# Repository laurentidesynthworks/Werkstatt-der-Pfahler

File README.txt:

The Werkstatt der Pfähler (Werkstatt the Impaler) is a Moog Werkstatt-Ø1 that has been cut up and extensively modified. There 
is a huge beast inside these little synths that can only be accessed through modifying.

There are 2 versions available: Standard and Full. The Standard version is perfect for incorporating into an existing Eurorack 
modular system. Most of the header patch points have been brought to the rear of the unit to 3.5mm Jacks. Most importantly, 
the EG can be triggered by an external gate. This is not possible without modification.  

The Full version takes the standard and brings it to a stand-alone powerhouse! In addition to the CV In’s and Out’s at the 
rear, buffers are added to all CV Out’s (these are circuits that keep critical voltages, like the raw VCO waveforms from 
sagging when used to drive external gear).  The CV Out’s are wired to TRS jacks, giving a total of 8 individual outputs. 
A MIDI 2 CV (MINICV) converter is added to drive the VCO and EG. Additionally, the CV & Gate generated by the MIDI 2 CV is 
brought to 2 jacks, so when the Werkstatt is not in use, it can be used to drive other analog gear that does not have MIDI,
but does have CV & Gate In’s. A mixer is added to give volume control over the Werkstatt VCO and External Audio. Additionally, 
the VCF is wired to the Audio In jack, so when nothing is plugged into the jack, the Audio In volume knob will send the VCF 
back into itself for some intense filter overdrive! A 2nd glide circuit is added in line with the VCO CV In. The Werkstatt 
Glide potentiometer is removed and replaced with a dual gang potentiometer. This way one knob can control both the Werkstatt 
glide and the external pitch glide. The VCO Wave selector switch is removed and a mixer circuit is added so the 2 waveforms 
can be continuously blended from one to the other. Lastly, there is a Fine Tune knob added.

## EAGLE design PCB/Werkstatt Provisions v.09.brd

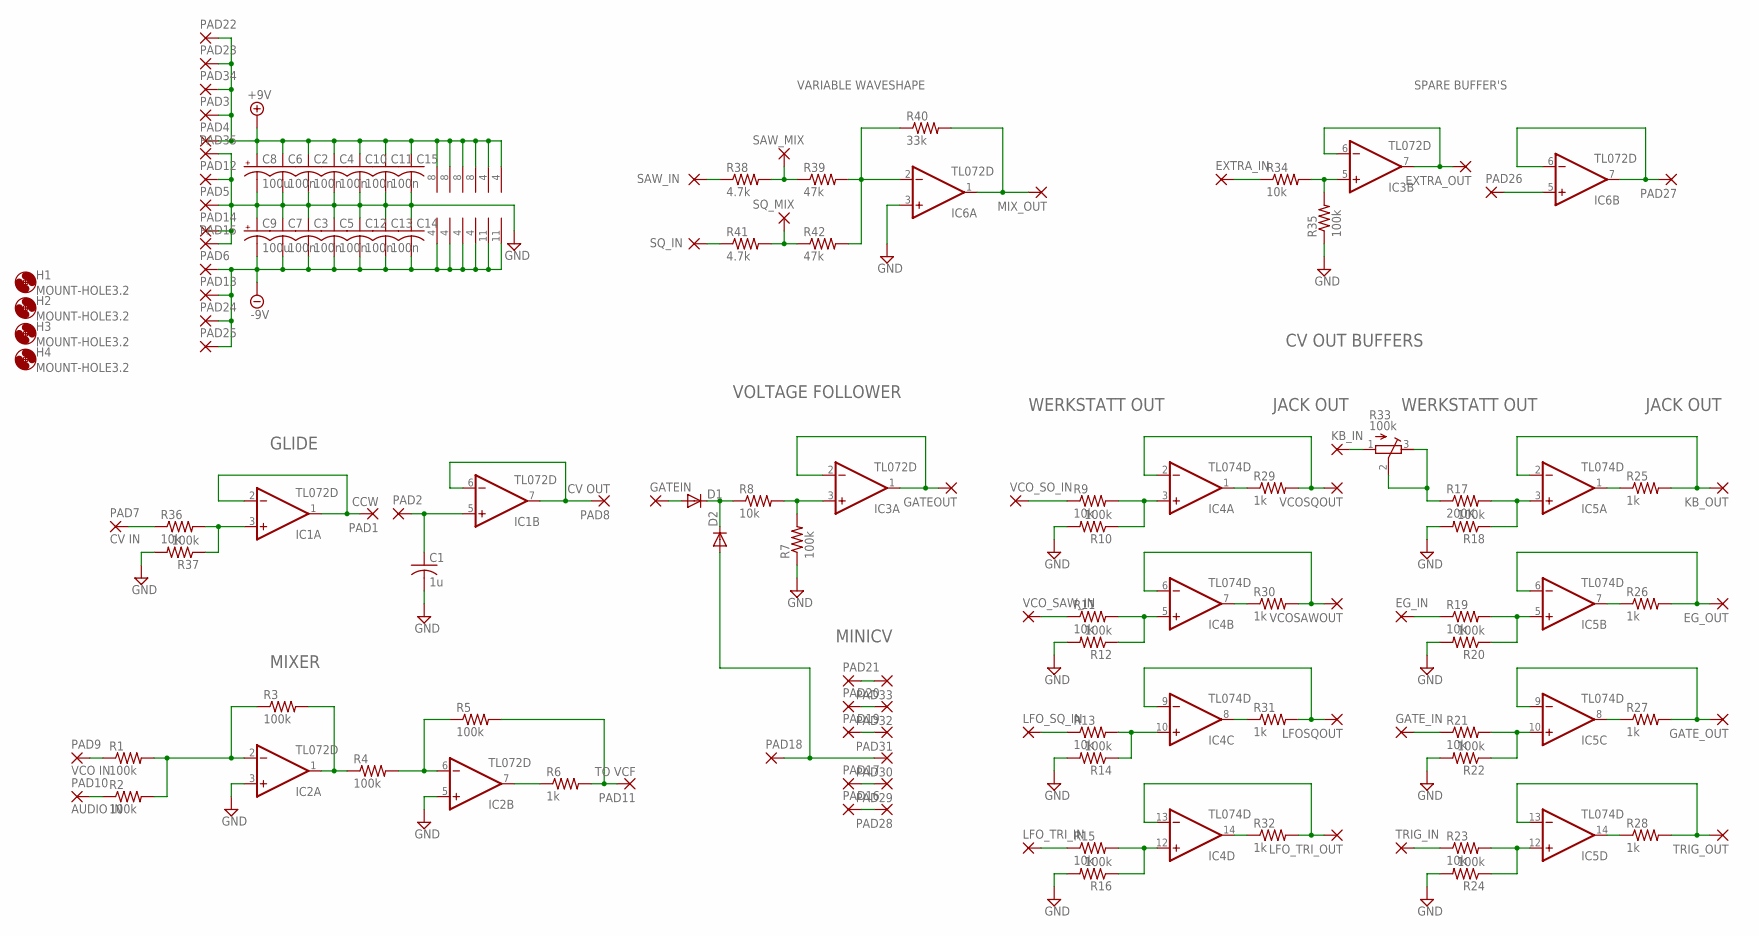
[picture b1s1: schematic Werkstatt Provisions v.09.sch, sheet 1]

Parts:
C1: 1u; C0805K
C2, C3, C4, C5, C6, C7, C10, C11, C12, C13: 100n; C0805K
C8, C9: 100u; PANASONIC_D
C14, C15: C-USC0805; C0805
D1, D2: DIODE-SOD323-W; SOD323-W
EG_IN: 2,0/0,9-O
EG_OUT: 2,0/0,9-O
EXTRA_IN: 2,0/0,9-O
EXTRA_OUT: 2,0/0,9-O
GATEIN: 2,0/0,9-O
GATEOUT: 2,0/0,9-O
GATE_IN: 2,0/0,9-O
GATE_OUT: 2,0/0,9-O
H1, H2, H3, H4: MOUNT-HOLE3.2; 3,2
IC1, IC2, IC3, IC6: TL072D; SO08
IC4, IC5: TL074D; SO14
KB_IN: 2,0/0,9-O
KB_OUT: 2,0/0,9-O
LFOSQOUT: 2,0/0,9-O
LFO_SQ_IN: 2,0/0,9-O
LFO_TRI_IN: 2,0/0,9-O
LFO_TRI_OUT: 2,0/0,9-O
MIX_OUT: 2,0/0,9-O
PAD1: CCW; 2,0/0,9-O
PAD2, PAD3, PAD4, PAD5, PAD6, PAD12, PAD13, PAD14, PAD15, PAD16, PAD17, PAD18, PAD19, PAD20, PAD21, PAD22, PAD23, PAD24, PAD25, PAD26, PAD27: 2,0/0,9-O
PAD7: CV IN; 2,0/0,9-O
PAD8: CV OUT; 2,0/0,9-O
PAD9: VCO IN; 2,0/0,9-O
PAD10: AUDIO IN; 2,0/0,9-O
PAD11: TO VCF; 2,0/0,9-O
PAD28, PAD29, PAD30, PAD31, PAD32, PAD33, PAD34, PAD35: 1,6/0,8
R1, R2, R3, R4, R5, R7, R10, R12, R14, R16, R18, R20, R22, R24, R35, R37: 100k; M0805
R6, R25, R26, R27, R28, R29, R30, R31, R32: 1k; M0805
R8, R9, R11, R13, R15, R19, R21, R23, R34, R36: 10k; M0805
R17: 200K; M0805
R33: 100k; RTRIM3202
R38, R41: 4.7k; R0805
R39, R42: 47k; R0805
R40: 33k; R0805
SAW_IN: 2,0/0,9-O
SAW_MIX: 2,0/0,9-O
SQ_IN: 2,0/0,9-O
SQ_MIX: 2,0/0,9-O
TRIG_IN: 2,0/0,9-O
TRIG_OUT: 2,0/0,9-O
VCOSAWOUT: 2,0/0,9-O
VCOSQOUT: 2,0/0,9-O
VCO_SAW_IN: 2,0/0,9-O
VCO_SO_IN: 2,0/0,9-O

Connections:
+9V: C2.1, C4.1, C6.1, C8.+, C10.1, C11.1, C15.1, IC1.8 (V+), IC2.8 (V+), IC3.8 (V+), IC4.4 (V+), IC5.4 (V+), IC6.8 (V+), PAD3.1, PAD4.1, PAD22.1, PAD23.1, PAD34.1
-9V: C3.2, C5.2, C7.2, C9.-, C12.2, C13.2, C14.2, IC1.4 (V-), IC2.4 (V-), IC3.4 (V-), IC4.11 (V-), IC5.11 (V-), IC6.4 (V-), PAD6.1, PAD13.1, PAD24.1, PAD25.1
GATE_IN_MIDI: D2.A, PAD18.1, PAD30.1
GND: C1.2, C2.2, C3.1, C4.2, C5.1, C6.2, C7.1, C8.-, C9.+, C10.2, C11.2, C12.1, C13.1, C14.1, C15.2, IC2.3 (+IN), IC2.5 (+IN), IC6.3 (+IN), PAD5.1, PAD12.1, PAD14.1, PAD15.1, PAD35.1, R7.1, R10.2, R12.2, R14.2, R16.2, R18.2, R20.2, R22.2, R24.2, R35.1, R37.2
LSW: D1.A, GATEIN.1
unnamed: IC1.1 (OUT), IC1.2 (-IN), PAD1.1
unnamed: PAD7.1, R36.1
unnamed: C1.1, IC1.5 (+IN), PAD2.1
unnamed: IC1.6 (-IN), IC1.7 (OUT), PAD8.1
unnamed: IC2.2 (-IN), R1.2, R2.2, R3.1
unnamed: PAD16.1, PAD28.1
unnamed: IC2.1 (OUT), R3.2, R4.1
unnamed: IC2.6 (-IN), R4.2, R5.1
unnamed: PAD11.1, R5.2, R6.2
unnamed: IC2.7 (OUT), R6.1
unnamed: PAD9.1, R1.1
unnamed: PAD10.1, R2.1
unnamed: IC3.5 (+IN), R34.2, R35.2
unnamed: IC3.3 (+IN), R7.2, R8.2
unnamed: PAD17.1, PAD29.1
unnamed: GATEOUT.1, IC3.1 (OUT), IC3.2 (-IN)
unnamed: PAD19.1, PAD31.1
unnamed: PAD20.1, PAD32.1
unnamed: PAD21.1, PAD33.1
unnamed: D1.C, D2.C, R8.1
unnamed: IC1.3 (+IN), R36.2, R37.1
unnamed: R9.1, VCO_SO_IN.1
unnamed: IC4.3 (+IN), R9.2, R10.1
unnamed: EG_IN.1, R19.1
unnamed: R11.1, VCO_SAW_IN.1
unnamed: IC4.5 (+IN), R11.2, R12.1
unnamed: IC4.2 (-IN), R29.2, VCOSQOUT.1
unnamed: IC4.6 (-IN), R30.2, VCOSAWOUT.1
unnamed: IC4.9 (-IN), LFOSQOUT.1, R31.2
unnamed: IC4.13 (-IN), LFO_TRI_OUT.1, R32.2
unnamed: IC5.2 (-IN), KB_OUT.1, R25.2
unnamed: EG_OUT.1, IC5.6 (-IN), R26.2
unnamed: GATE_OUT.1, IC5.9 (-IN), R27.2
unnamed: IC5.13 (-IN), R28.2, TRIG_OUT.1
unnamed: LFO_TRI_IN.1, R15.1
unnamed: IC4.14 (OUT), R32.1
unnamed: LFO_SQ_IN.1, R13.1
unnamed: IC4.10 (+IN), R13.2, R14.1
unnamed: IC4.12 (+IN), R15.2, R16.1
unnamed: IC4.8 (OUT), R31.1
unnamed: IC4.1 (OUT), R29.1
unnamed: IC4.7 (OUT), R30.1
unnamed: IC5.5 (+IN), R19.2, R20.1
unnamed: IC5.10 (+IN), R21.2, R22.1
unnamed: GATE_IN.1, R21.1
unnamed: R23.1, TRIG_IN.1
unnamed: R17.1, R33.2 (S), R33.3 (A)
unnamed: IC5.3 (+IN), R17.2, R18.1
unnamed: IC5.12 (+IN), R23.2, R24.1
unnamed: IC5.14 (OUT), R28.1
unnamed: IC5.8 (OUT), R27.1
unnamed: IC5.7 (OUT), R26.1
unnamed: IC5.1 (OUT), R25.1
unnamed: KB_IN.1, R33.1 (E)
unnamed: EXTRA_IN.1, R34.1
unnamed: IC6.2 (-IN), R39.2, R40.1, R42.2
unnamed: EXTRA_OUT.1, IC3.6 (-IN), IC3.7 (OUT)
unnamed: R41.2, R42.1, SQ_MIX.1
unnamed: R41.1, SQ_IN.1
unnamed: R38.2, R39.1, SAW_MIX.1
unnamed: R38.1, SAW_IN.1
unnamed: IC6.1 (OUT), MIX_OUT.1, R40.2
unnamed: IC6.6 (-IN), IC6.7 (OUT), PAD27.1
unnamed: IC6.5 (+IN), PAD26.1

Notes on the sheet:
GLIDE
MIXER
VOLTAGE FOLLOWER
CV OUT BUFFERS
WERKSTATT OUT
JACK OUT
MINICV
SPARE BUFFER'S
VARIABLE WAVESHAPE

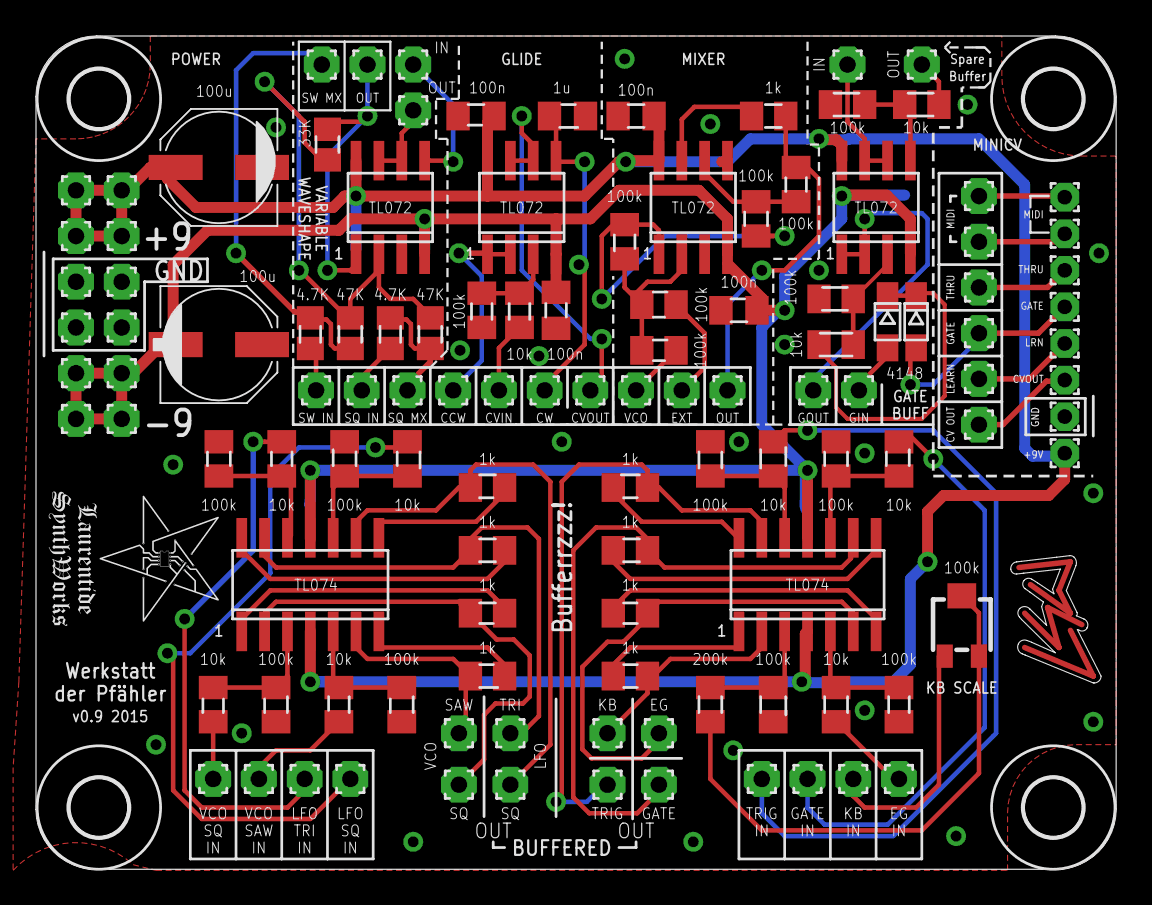
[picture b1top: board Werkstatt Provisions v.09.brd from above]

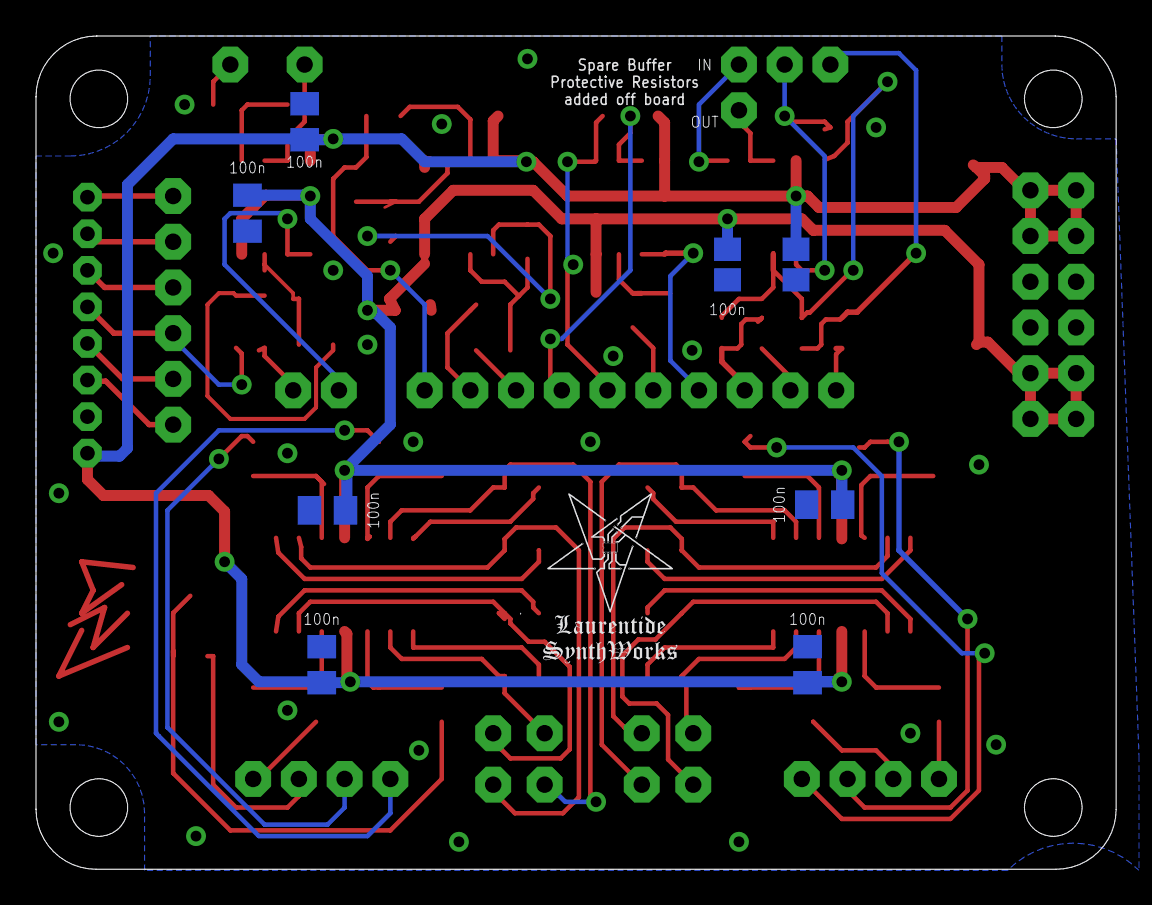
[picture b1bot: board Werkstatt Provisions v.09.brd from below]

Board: 2 copper layers, 60.0 x 46.3 mm, 129 parts (8 on the bottom side), 69 nets.

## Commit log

2015-01-19 :octocat: Added .gitattributes & .gitignore files
2015-01-19 Changed through hole trimmer to SMD
2015-01-19 README
2015-01-19 Front Panel Express
